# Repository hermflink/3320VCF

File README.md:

# 3320VCF
Kicad project files of a CEM3320/AS3320 based VCF. Part of a modular DIY synth project, other modules to follow in other repositories. 

Used the Audio.lib from https://kicad.github.io/symbols/Audio to extend the Kicad library for the AS3320 component.

Designed to work with +/- 15V, but will most likely work fine for +/- 12V as well

The PCB is 9.5 x 5.5 cm and has no PCB-mounting of potmeters, switches, jacks; these are all connected by pin header connectors

Stages 1 and 2 are switchable between HP and LP mode by SW1 and SW2. 
Stages 3 and 4 are fixed on LP mode.
These allow for the following filter modes:
- A: 24dB LP
- B: 12dB BP
- C: 6dB HP + 18dB LP
- D: 6dB LP + 6dB HP + 12dB LP

Background of the mode configurations: https://electricdruid.net/multimode-filters-part-1-reconfigurable-filters/ section Craig Anderton’s Multiple Identity Filter.

Capacitors on pin 4, 5, 11 and 16 should be 1% or less tolerance! 

F1 and F2 fuses are not really required and can be replaced by shorts.

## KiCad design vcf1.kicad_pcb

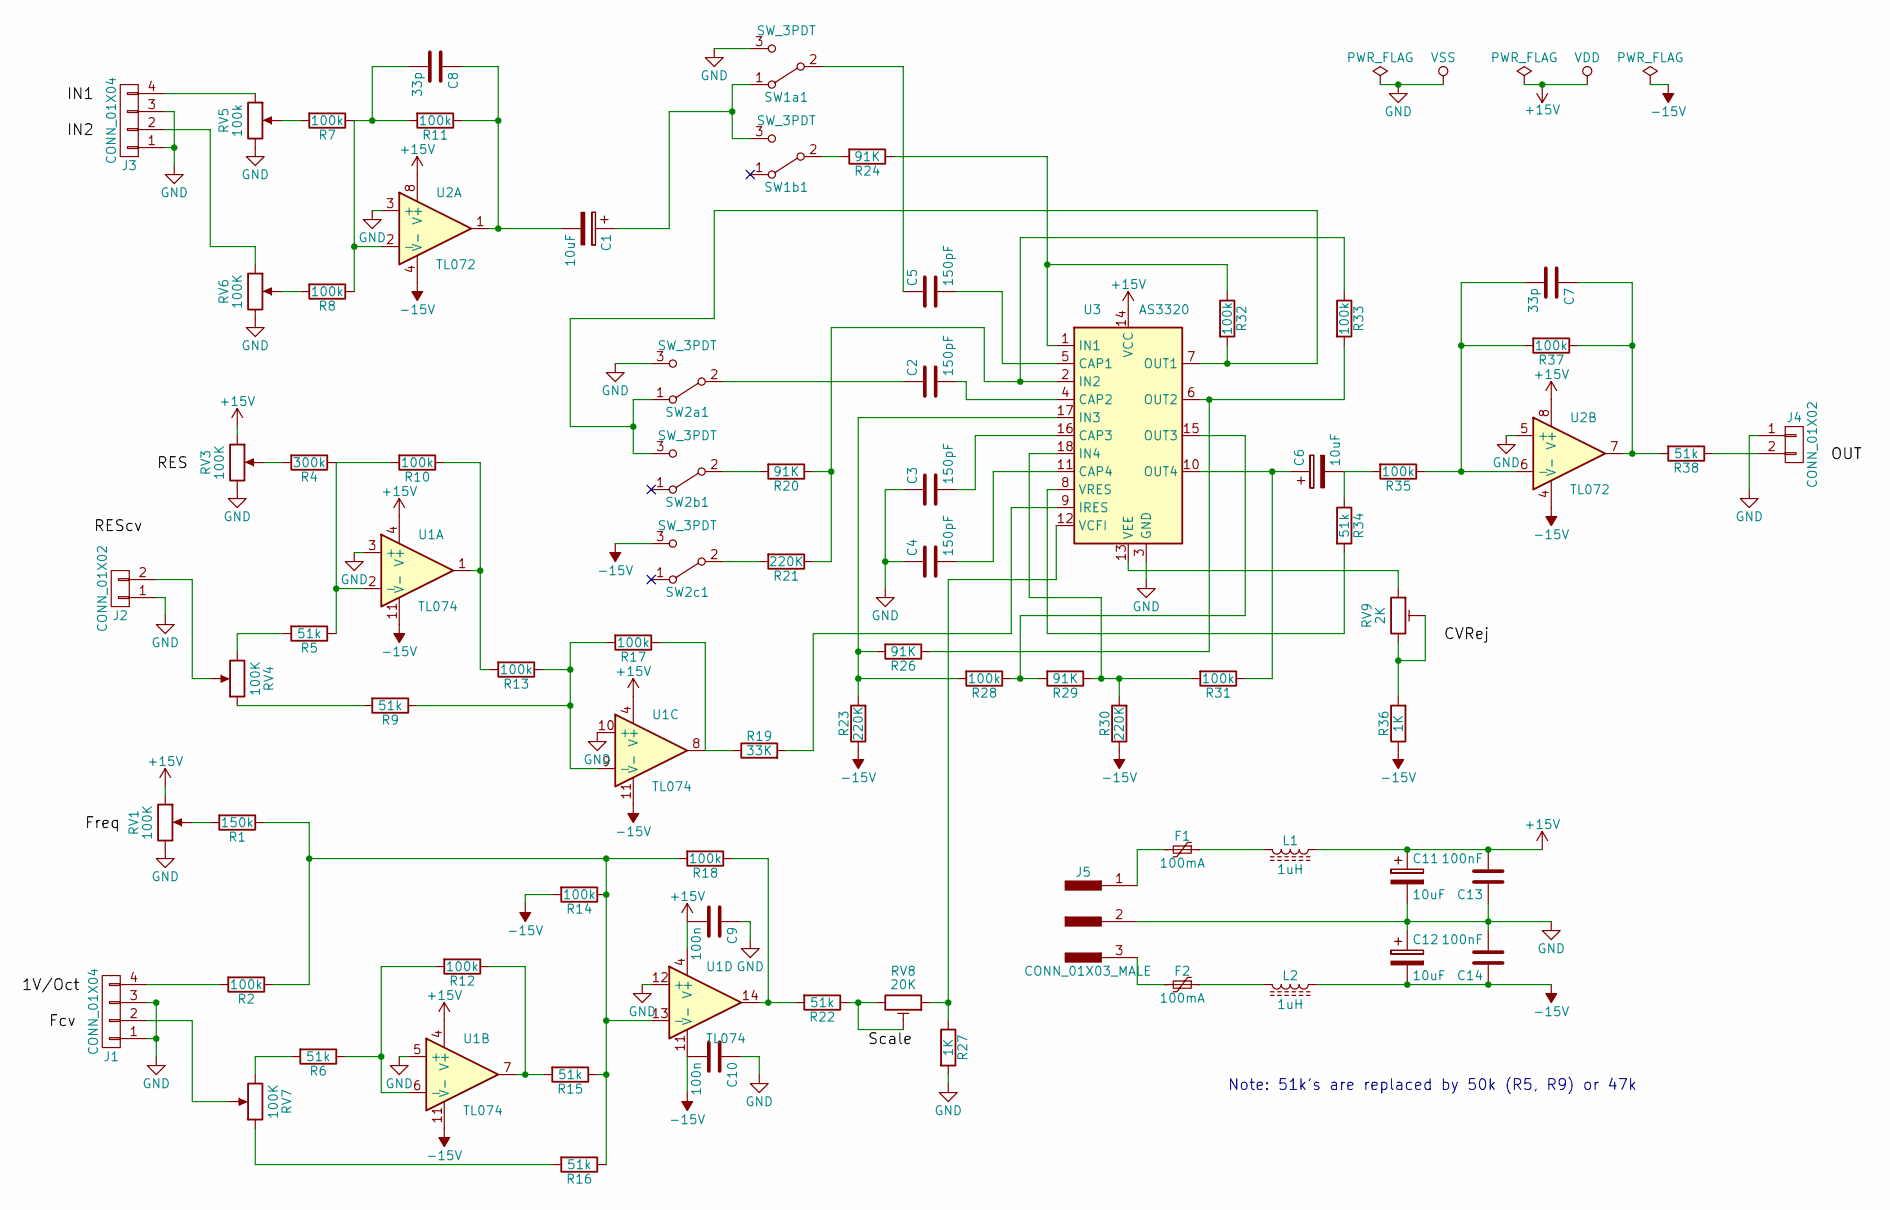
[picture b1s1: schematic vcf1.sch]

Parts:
C1, C6, C11, C12: 10uF; CP_Radial_D5.0mm_P2.00mm
C2, C3, C4, C5: 150pF; R_Axial_DIN0309_L9.0mm_D3.2mm_P2.54mm_Vertical
C7, C8: 33p; C_Disc_D5.0mm_W2.5mm_P5.00mm
C9, C10: 100n; C_Disc_D5.0mm_W2.5mm_P5.00mm
C13, C14: 100nF; C_Disc_D5.0mm_W2.5mm_P5.00mm
F1, F2: 100mA; C_Disc_D6.0mm_W2.5mm_P5.00mm
J1, J3: CONN_01X04; Pin_Header_Straight_1x04_Pitch2.54mm
J2, J4: CONN_01X02; Pin_Header_Straight_1x02_Pitch2.54mm
J5: CONN_01X03_MALE; Pin_Header_Straight_1x03_Pitch2.54mm
L1, L2: 1uH; L_Axial_L9.5mm_D4.0mm_P2.54mm_Vertical_Fastron_SMCC
R1: 150k; R_Axial_DIN0207_L6.3mm_D2.5mm_P2.54mm_Vertical
R2, R7, R8, R10, R11, R12, R13, R14, R17, R18, R28, R31, R32, R33, R35, R37: 100k; R_Axial_DIN0207_L6.3mm_D2.5mm_P2.54mm_Vertical
R4: 300k; R_Axial_DIN0207_L6.3mm_D2.5mm_P2.54mm_Vertical
R5, R6, R9, R15, R16, R22, R34, R38: 51k; R_Axial_DIN0207_L6.3mm_D2.5mm_P2.54mm_Vertical
R19: 33K; R_Axial_DIN0207_L6.3mm_D2.5mm_P2.54mm_Vertical
R20, R24, R26, R29: 91K; R_Axial_DIN0207_L6.3mm_D2.5mm_P10.16mm_Horizontal
R21, R23, R30: 220K; R_Axial_DIN0207_L6.3mm_D2.5mm_P2.54mm_Vertical
R27, R36: 1K; R_Axial_DIN0207_L6.3mm_D2.5mm_P2.54mm_Vertical
RV1, RV3, RV4, RV6, RV7: 100K; Potentiometer_WirePads_Small
RV5: 100k; Potentiometer_WirePads_Small
RV8: 20K; Potentiometer_Trimmer_Bourns_3296W
RV9: 2K; Potentiometer_Trimmer_Bourns_3296W
SW1a1, SW1b1, SW2a1, SW2b1, SW2c1: SW_3PDT; Pin_Header_Straight_1x03_Pitch2.54mm
U1: TL074; DIP-14_W7.62mm_Socket
U2: TL072; DIP-8_W7.62mm_Socket
U3: AS3320; DIP-18_W7.62mm

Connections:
+15V: C9.2, C11.1, C13.2, L1.1, RV1.1, RV3.1, U1.4 (V+), U2.8 (V+), U3.14 (VCC)
-15V: C10.2, C12.2, C14.1, L2.1, R14.2, R23.1, R30.1, R36.1, SW2c1.3 (C), U1.11 (V-), U2.4 (V-)
GND: C3.1, C4.1, C9.1, C10.1, C11.2, C12.1, C13.1, C14.2, J1.1, J1.3, J2.1, J3.1, J3.3, J4.1, J5.2, R27.2, RV1.3, RV3.3, RV5.3, RV6.3, SW1a1.3 (C), SW2a1.3 (C), U1.3 (+), U1.5 (+), U1.10 (+), U1.12 (+), U2.3 (+), U2.5 (+), U3.3 (GND)
unnamed: C1.1, SW1a1.1 (A), SW1b1.3 (C)
unnamed: C1.2, C8.1, R11.1, U2.1
unnamed: C2.1, SW2a1.2 (B)
unnamed: C2.2, U3.4 (CAP2)
unnamed: C3.2, U3.16 (CAP3)
unnamed: C4.2, U3.11 (CAP4)
unnamed: C5.1, SW1a1.2 (B)
unnamed: C5.2, U3.5 (CAP1)
unnamed: C6.1, R31.1, U3.10 (OUT4)
unnamed: C6.2, R34.1, R35.2
unnamed: C7.1, R37.1, R38.2, U2.7
unnamed: C7.2, R35.1, R37.2, U2.6 (-)
unnamed: C8.2, R7.1, R8.1, R11.2, U2.2 (-)
unnamed: F1.1, L1.2
unnamed: F1.2, J5.1
unnamed: F2.1, L2.2
unnamed: F2.2, J5.3
unnamed: J1.2, RV7.2
unnamed: J1.4, R2.2
unnamed: J2.2, RV4.2
unnamed: J3.2, RV6.1
unnamed: J3.4, RV5.1
unnamed: J4.2, R38.1
unnamed: R1.1, R2.1, R14.1, R15.1, R16.1, R18.2, U1.13 (-)
unnamed: R1.2, RV1.2
unnamed: R4.2, RV3.2
unnamed: R5.2, RV4.3
unnamed: R6.2, RV7.3
unnamed: R7.2, RV5.2
unnamed: R8.2, RV6.2
unnamed: R9.2, RV4.1
unnamed: R10.1, R13.2, U1.1
unnamed: R4.1, R5.1, R10.2, U1.2 (-)
unnamed: R12.1, R15.2, U1.7
unnamed: R6.1, R12.2, U1.6 (-)
unnamed: R9.1, R13.1, R17.2, U1.9 (-)
unnamed: R16.2, RV7.1
unnamed: R17.1, R19.1, U1.8
unnamed: R18.1, R22.2, U1.14
unnamed: R19.2, U3.9 (IRES)
unnamed: R20.1, R21.1, R33.1, U3.2 (IN2)
unnamed: R20.2, SW2b1.2 (B)
unnamed: R21.2, SW2c1.2 (B)
unnamed: R22.1, RV8.2, RV8.3
unnamed: R23.2, R26.2, R28.2, U3.17 (IN3)
unnamed: R24.1, R32.1, U3.1 (IN1)
unnamed: R24.2, SW1b1.2 (B)
unnamed: R26.1, R33.2, U3.6 (OUT2)
unnamed: R27.1, RV8.1, U3.12 (VCFI)
unnamed: R28.1, R29.2, U3.15 (OUT3)
unnamed: R29.1, R30.2, R31.2, U3.18 (IN4)
unnamed: R32.2, SW2a1.1 (A), SW2b1.3 (C), U3.7 (OUT1)
unnamed: R34.2, U3.8 (VRES)
unnamed: R36.2, RV9.2, RV9.3
unnamed: RV9.1, U3.13 (VEE)

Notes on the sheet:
Note: 51k's are replaced by 50k (R5, R9) or 47k

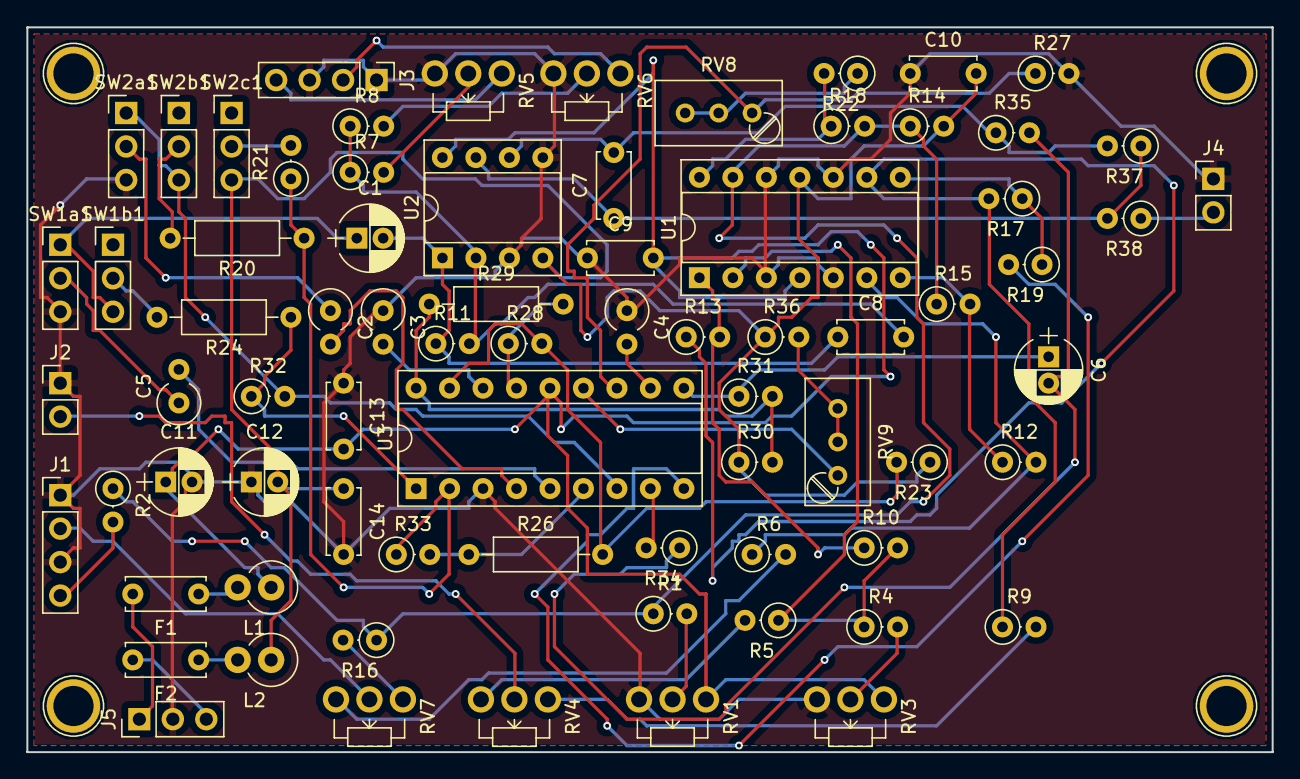
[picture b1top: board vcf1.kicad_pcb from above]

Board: 2 copper layers, 94.5 x 55.0 mm, 75 parts (0 on the bottom side), 58 nets.

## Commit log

2019-05-28 Add files via upload
    First commit VCF v1
2019-11-08 Create LICENSE
